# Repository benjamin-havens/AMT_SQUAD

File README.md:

# AMT_SQUAD

This repo is used for transmitting and receiving radio frequencies over B210 radios

Item number for antenna: PE51RD1031 </br>
Antenna name: 4.5 dBi MultiBand Rubber Duck Portable Antenna 615-4200 MHz SMA Connector

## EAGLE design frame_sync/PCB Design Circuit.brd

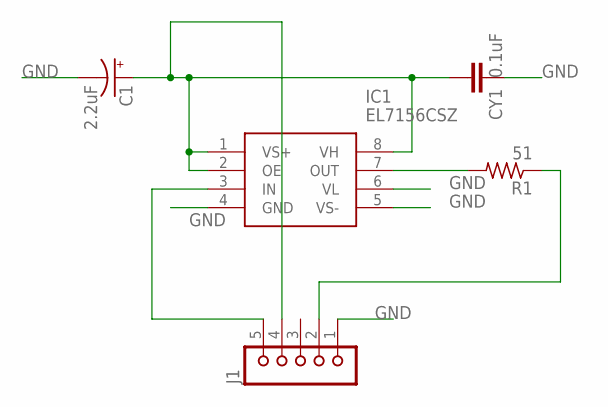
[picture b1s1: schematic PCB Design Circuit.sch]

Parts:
C1: 2.2uF; E2,5-6
CY1: 0.1uF; YC7B5
IC1: EL7156CSZ; SOIC127P599X173-8N
J1: JU05
R1: 51; 0207/7

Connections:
GND: C1.-, CY1.1, IC1.4 (GND), IC1.5 (VS-), IC1.6 (VL), J1.1
unnamed: IC1.3 (IN), J1.5
unnamed: IC1.7 (OUT), R1.2
unnamed: C1.+, CY1.2, IC1.1 (VS+), IC1.2 (OE), IC1.8 (VH), J1.4
unnamed: J1.2, R1.1

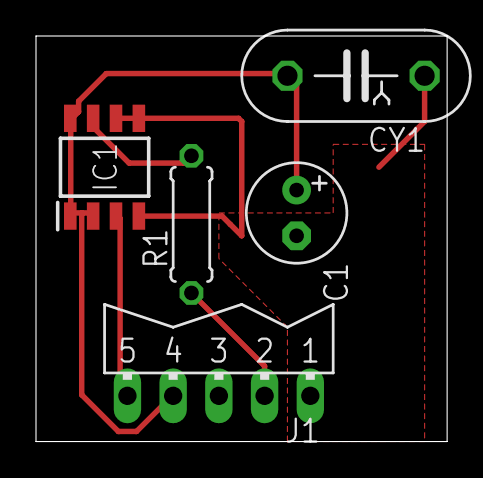
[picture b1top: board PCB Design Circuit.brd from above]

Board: 2 copper layers, 22.8 x 22.5 mm, 5 parts (0 on the bottom side), 5 nets.

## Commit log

2022-05-17 Commit tx
2022-05-17 Adding matlab code for receiver and plotting
2022-05-18 Changed Rx filename and screenshot filenames
2022-05-18 changed rx file and added csv to results
2022-05-19 Update tx to while loop and correct sampling rate. Deleted screenshots folder
2022-05-19 Cleaned up, commented, added plotting from CSV file, and plotted test data from 5-18-22
2022-05-19 Update file names for consistency
2022-05-19 Actually updated code for the Rx
2022-05-19 Actually updated Rx file
2022-05-19 Commented and added for loop to Rx
2022-05-19 Added Dr Rice's test file for 5-18-22
2022-05-19 Cleaned up Rx and Tx code and added 1e6 samples per frame to receiver
2022-05-19 Removed for loop from Rx and removed .gitignore from itself
2022-05-19 Added results from close and far wireless tests (5/19/22)
2022-05-19 Organized results into weeks and update Tx
2022-05-19 added results for hallway tests
2022-05-19 moved csv files
2022-05-19 Enabled burst mode and switched Tx to transmit only one burst
2022-05-20 Added capability to rx to receive on a and b channels
2022-05-20 Reverted from burst mode in Tx
2022-05-20 Made a plotting script to plot output of both channels, and modified tx and rx slightly to make repeated transmission easier
2022-05-20 Correct tx comments
2022-05-20 Results from V vs H tx antenna experiment
2022-05-24 Created MATLAB and python folders. Created transmit_cosine.py
2022-05-24 Updated print statements in tx_cosine and updated gitignore
2022-05-24 Added plotting utility, updated rx to reflect that, standardized api importing in rx and tx
2022-05-24 Updated plotting to include fft, updated Rx to plot fft, updated Tx calling params
2022-05-24 Updated .gitignore
2022-05-25 Changed comments in plot and added options to fft
2022-05-25 Fixed tx cos function
2022-05-25 Updated variable name of lpef in tx cos
2022-05-25 Added capability to suppress terminal output, used it in tx cos
2022-05-26 updated agc
2022-05-26 Just added the plots for one channel, currently commented out
2022-05-26 Added new results folder
2022-05-26 added pictures of our results for today
2022-05-26 Got rid of tmp.txt
2022-05-26 Changed result graphs names
2022-05-27 Added gridlines and fixed chart labels
2022-05-27 Added .vscode/ to .gitignore
2022-05-27 Removed redundant code
2022-05-27 Added capability to write to csv path in uhd_params.py
2022-05-27 added file with channel tests
2022-05-27 Added to channel comparison
2022-05-27 Added label of max freq amplitude to fft plots
2022-05-27 added further results to the channel test
2022-06-01 Added test files from the gnu radio API
2022-06-01 allows runtime adjustment of variables
2022-06-02 "Added new results folder for this week"
2022-06-02 Added ability to plot in dB or not
2022-06-02 removing files that I accidentally added to the wrong week
2022-06-03 June 3rd test results
2022-06-03 Added capability to keep y axis limits the same when plotting for two channels, removed extraneous transmit import
2022-06-03 Updated receive.py to be able to specify different gains on a channel. You must make some changes in the uhd module for this to work
2022-06-03 Wired Tests
2022-06-06 Results for June 6th
2022-06-07 Added a file for receiving real-time with the gnu software
2022-06-07 Added a description to the plots so it's easier to tell what the settings were for each graph
2022-06-09 updated spectrum analyzer
2022-06-09 removed redundant receive file
2022-06-09 Updated descriptions in graphs and today's test results
2022-06-09 Create Results Written
2022-06-09 Made description items user inputs and moved plot tight
2022-06-09 Moved results written file and formatted plotting
2022-06-09 Added input gate before transmitting and receiving
2022-06-09 Fixed plotting one channel
2022-06-09 tiny change
2022-06-09 Fixed things and added results
2022-06-09 Added data for left radio
2022-06-09 cleaned up separate radio results
2022-06-10 todays results
2022-06-10 added results from separate radios
2022-06-10 added ability to name csv file to save
2022-06-12 only save csv if you name it
2022-06-12 june 11 test results
2022-06-12 renamed file
2022-06-13 Added the csv files after removing csv from the gitignore
2022-06-13 added files with the sounding signal
2022-06-13 Updated write to csv
2022-06-13 new csv
2022-06-13 added files for parsing csv files
2022-06-14 Added pictures from the june 11th test and cleaned up some file structure things
2022-06-14 created folder called testing for files that are separate from the experimental data we gathered
2022-06-14 updates to matlab receive and plot in matlab and updated gnu radio to only get one channel
2022-06-15 changed tx code
2022-06-15 updated matlab plot code
2022-06-15 modified Tx file
2022-06-15 found the problem!
2022-06-15 idk what changed, but im pushing it
2022-06-17 June 16 results
2022-06-17 added file to make impusle response
2022-06-17 Fixed permissions on csv and cleaned up find impulse response, added capability to find two at once
2022-06-17 Fixed indices in find impulse response
2022-06-17 Updated impulse response finder to find optimal h1 and h2
2022-06-17 added folder for .mat files
2022-06-17 Finished pruning algo
2022-06-17 added more folders
2022-06-17 .mat files for 20-50 with_hc
2022-06-17 addded impulse responses
2022-06-17 Added with_hc 0 & 10 and wo_hc 0 & 10
2022-06-17 20-50 ab with hc IRs
2022-06-17 added wired test results to results/june_16
2022-06-18 added folder for pictures
2022-06-18 added some examples of the pruning process
2022-06-19 Fixed an error, multiplied B by 8/9, and reran the make impulse response on all csvs
2022-06-20 added and unzipped the files sent by Dr. Rice
2022-06-21 New files from Dr Rice.
2022-06-21 Moved Dr Rice's files to matlab directory
2022-06-21 updated the file that Dr. Rice changed
2022-06-21 removed duplicate files
2022-06-21 Added text file with additional pruning (add_pruning.txt)
2022-06-21 testing push
2022-06-21 Repruned all IR's, added max index checking, added format for N0/BER results, and updated gitignore
2022-06-21 Repruned IRs for real this time
2022-06-21 Modified gitignore and removed slprj
2022-06-21 Updated plotting in Reprune and fixed comments in makeBERPlot
2022-06-23 Added an example plot to the bottom and some data
2022-06-23 Formatting for Reprune.m
2022-06-24 added results from ber simulations and june 23 test
2022-06-24 fixed typo in gitignore
2022-06-24 with_hc results from tests on June 23
2022-06-24 Generated new impulse responses and repruned them using new indices.
2022-06-24 added june 24th results
2022-06-24 results from june_24 tests wo_hc
2022-06-24 More simulation results
2022-06-24 Moved result csvs around and began pruning process for take_4
2022-06-24 Update makeBERPlot.m
    added ber plot coordinates for 70-90 with_hc
2022-06-24 Repruned take_4
2022-06-24 Update makeBERPlot.m
    added data for 60b w/ hc
2022-06-24 More take 4 pruning
2022-06-24 updated weird .mat files
    updated weird .mat files
2022-06-28 upadted makeBERPlot.m with our data
2022-06-28 added more data
2022-06-28 More results from makeBERPlot.m
2022-06-30 New plots and results
2022-06-30 .mat file with results
2022-07-06 added my presentation
2022-07-12 Updated gitignore, results for conference paper
2022-07-12 Created folder for old project and for new one, saved pn11 in new folder
2022-07-12 Fixed pn11 file
2022-07-14 added Joe's presentation
2022-07-14 Added folder with vivado set up
2022-07-14 added file with error set up messages and part #
2022-07-14 added sv pn11 file
2022-07-15 added pilot functionality
2022-07-18 updated tx_top file among other things
2022-07-18 fixed edge cases on pn11 generation
2022-07-19 new stuff from 7/19
2022-07-21 made the fpga code actually good
2022-08-04 added pcb schematics
2022-08-05 Start of the frame synchronizer code
2022-08-05 removed weird files
2022-08-05 Correlation function L6q first draft
2022-08-05 5 August wired test data
2022-08-05 Fix for L6q
2022-08-09 Zipped big folders in results folder
2022-08-09 Better frame sync functions, simulated transmission using old IRs
2022-08-09 Added check_results and formatted L0_L6
2022-08-10 Minor changes to check results and initial FSSM commit
2022-08-10 Beginning implementation of FSSM in python
2022-08-11 Moved wired test results to data folder, implemented FSSM
2022-08-11 Some changes to FSSM
2022-08-25 new data from Aug 25
2022-08-25 updated for new results
2022-08-25 copied receive file to fram_sync folder
2022-09-02 started adding graphing functionality
2022-09-02 added results from aug 25
2022-09-02 fixed graphing issues
2022-09-08 added plotting for weird
2022-09-08 Added ability to plot the correlated data
2022-09-08 fixed some errors and made the plotting a function
2022-09-09 reverted to fix some plotting errors
2022-09-09 made plotting function for simplicity and consistency, also, added variable number of subplots to make within the function
2022-09-09 small updates to plotting
2022-09-13 set FSSM.py to be the code from alt_plotting branch
2022-09-13 changed L0_small to L0_temp
